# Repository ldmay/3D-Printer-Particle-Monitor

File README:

Overview

This project implements an air quality monitor system to monitor 3D printing emissions using an ESP32, BME680, SGP40, and SPS30 sensors. 

3D printing emissions are typically broken down into volatile organic compounds (VOC) and ultrafine particles. These can be harmful when inhaled and are associated with higher risks for various medical conditions. The sensors used were chosen to detect these matters. 

Hardware

The project uses an ESP32-WROVER-B mounted on the ESP32 DevKit C. This provides a microcontroller a variety of peripherals to connect the sensors, as well as WIFI capabilities to host its own webserver. 

The BME680 is a general atmospheric condition sensor. It can detect a variety of atmospheric conditions, including temperature and humidity, which is required for the operation of the SGP40. It also returns a rough indication of VOC count using its gas resistance measurement, which can be compared to the VOC index calculated by the SGP40. Gas resistance is measured in kOhm. The absolute value is meaningless, but deviation over time represents an increase or decrease in VOCs. A lower resistance denotes an increase in VOC count. 
The BSEC library allows for more precise VOC measurements. I plan to include it in the future. 

The SGP40 is used to detect VOCs. Given temperature and humidity inputs, it returns a VOC index between 1 (ideal air quality) and 500 (very poor air quality). This index has a baseline of 100, and deviations represent changes in VOC over time. 

The SPS30 sensor is used to determine ultrafine particle concentrations. It detects particle numbers concentrations in the range of 0-3000/cm³ and mass concentrations in the range of  1-1000µg/m³. It also returns a measure of typical particle size. 
The number and mass concentration outputs represent distinct bins. There are five particle concentration bins - PM0.5 to PM10 - and four mass concentration bins - PM1 to PM10. The number following "PM" refers to the upper bound of the particle diameter range in micrometres (e.g. PM2.5 covers all particles from 0.3 μm up to 2.5 μm in diameter). 

Circuit Description

Sensors are connected to the ESP32 using a shared I2C bus. 

Software Requirements

Project written using PlatformIO. The Arduino IDE can likely also be used, though I have not tested this. 

The following libraries are required: 
lib_deps = 
	adafruit/Adafruit BME680 Library@^2.0.6
	adafruit/Adafruit Unified Sensor
	adafruit/Adafruit BusIO
	adafruit/Adafruit SGP40 Sensor@^1.1.4
	sensirion/Sensirion Gas Index Algorithm
	sensirion/Sensirion I2C SPS30@^1.0.0
	esp32async/ESPAsyncWebServer@^3.10.3
	esp32async/AsyncTCP@^3.4.10

Ignore the following libraries: 
lib_ignore = 
	RPAsyncTCP
	ESPAsyncTCP

Usage

Prior to uploading the code, replace the WIFI_SSID and WIFI_PASS values with your local network credentials. To access the server, you must be connected to the same network as the ESP32. 

By default, the code will update sensor values every second. This can easily be modified by changing the TIMER_DELAY value. The SPS30 sensor cannot measure at a higher frequency than 1Hz. 

Once the circuit is set up and code is loaded to the ESP32, it will begin printing sensor values to the serial monitor. The ESP32 should also automatically set up a web server. The address should be printed to the serial monitor. Navigating to the address will reveal a simple dashboard displaying atmospheric variables and charts showing VOC and particle concentrations. 

Prior to measuring a print, the sensors should be given 5-10 minutes to set up baseline values. VOC measurements display deviation from previous measurements, rather than absolute values.

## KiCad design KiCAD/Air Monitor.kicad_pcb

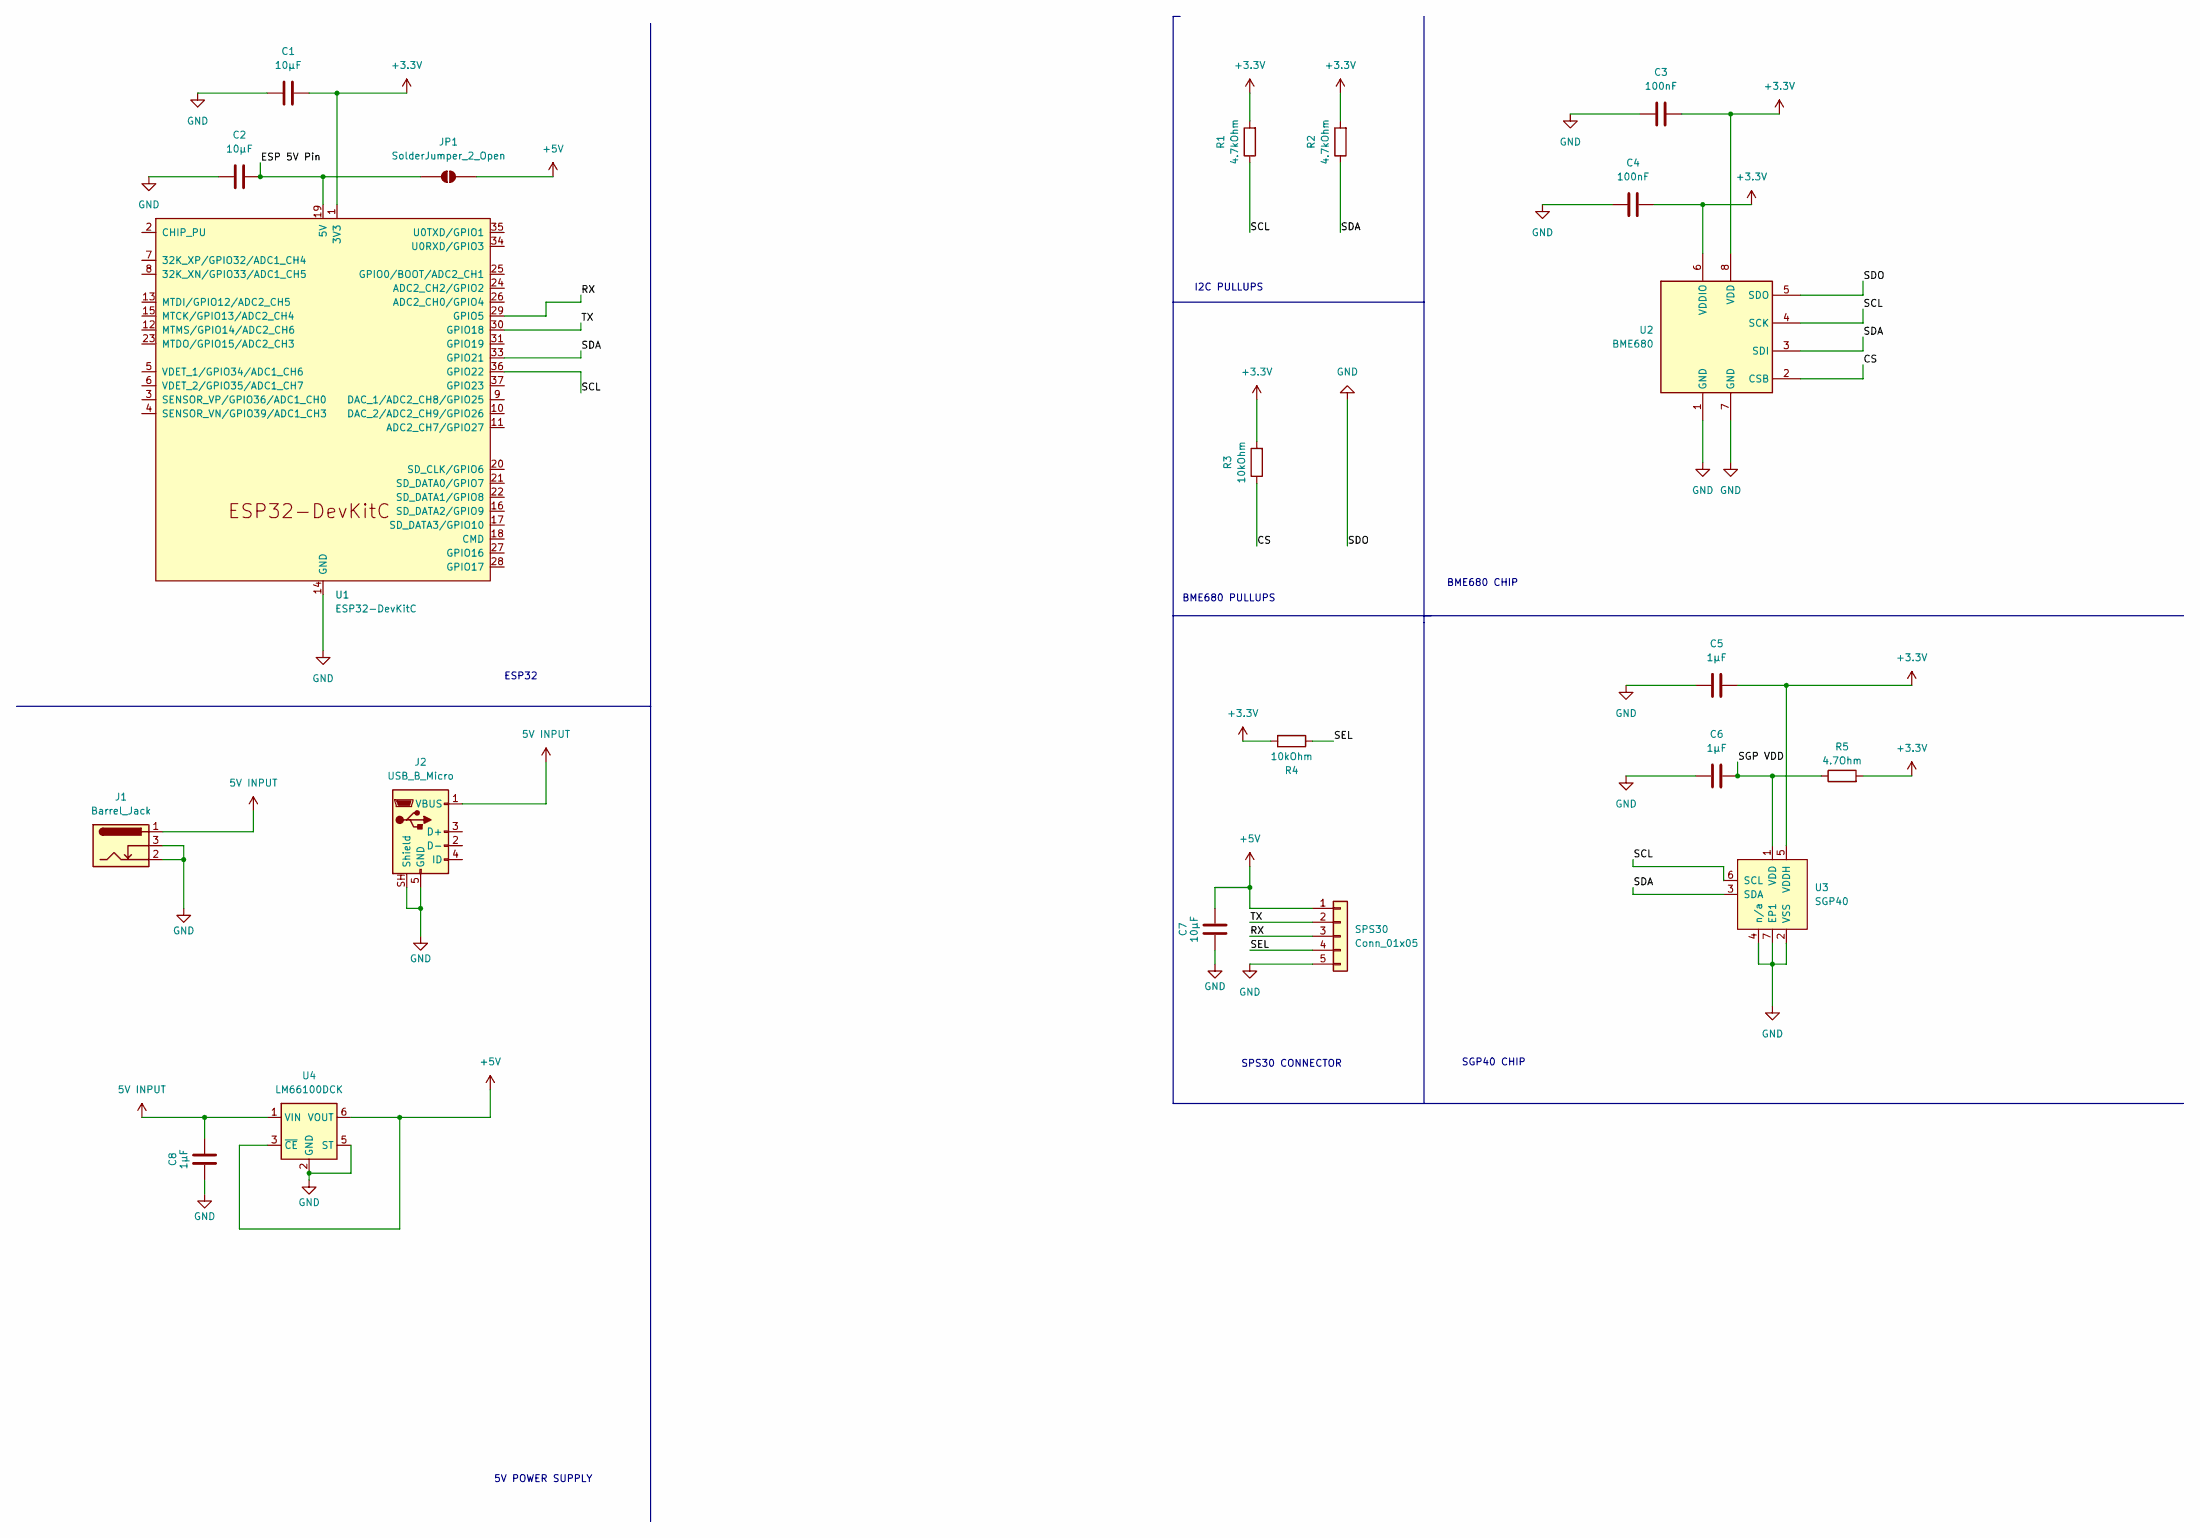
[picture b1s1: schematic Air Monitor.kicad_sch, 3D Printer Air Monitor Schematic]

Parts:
C1, C2, C7: 10μF; C_0402_1005Metric
C3, C4: 100nF; C_0402_1005Metric
C5, C6, C8: 1μF; C_0402_1005Metric
J1: Barrel_Jack; BarrelJack_Wuerth_6941xx301002
J2: USB_B_Micro; USB_Micro-B_Wuerth_629105150521
JP1: SolderJumper_2_Open; SolderJumper-2_P1.3mm_Open_RoundedPad1.0x1.5mm
R1, R2: 4.7kOhm; R_0402_1005Metric
R3, R4: 10kOhm; R_0402_1005Metric
R5: 4.7Ohm; R_0402_1005Metric
SPS30: Conn_01x05; JST_ZH_B5B-ZR_1x05_P1.50mm_Vertical
U1: ESP32-DevKitC; ESP32-DevKitC Shield
U2: BME680; Bosch_LGA-8_3x3mm_P0.8mm_ClockwisePinNumbering
U3: SGP40; Sensirion_DFN-6-1EP_2.44x2.44mm_P0.8mm
U4: LM66100DCK; SOT-363_SC-70-6

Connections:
5V INPUT: C8.2, J1.1, J2.1 (VBUS), U4.1 (VIN)
+3.3V: C1.2, C3.1, C4.1, C5.1, R1.2, R2.2, R3.2, R4.2, R5.2, U1.1 (3V3), U2.6 (VDDIO), U2.8 (VDD), U3.5 (VDDH)
+5V: C7.2, JP1.2 (B), SPS30.1, U4.3 (~CE), U4.6 (VOUT)
/CS: R3.1, U2.2 (CSB)
/ESP 5V Pin: C2.2, JP1.1 (A), U1.19 (5V)
/RX: SPS30.3, U1.29 (GPIO5)
/SCL: R1.1, U1.36 (GPIO22), U2.4 (SCK), U3.6 (SCL)
/SDA: R2.1, U1.33 (GPIO21), U2.3 (SDI), U3.3 (SDA)
/SEL: R4.1, SPS30.4
/SGP VDD: C6.1, R5.1, U3.1 (VDD)
/TX: SPS30.2, U1.30 (GPIO18)
GND: C1.1, C2.1, C3.2, C4.2, C5.2, C6.2, C7.1, C8.1, J1.2, J1.3, J2.5 (GND), J2.SH (Shield), SPS30.5, U1.14 (GND), U1.32 (GND), U1.38 (GND), U2.1 (GND), U2.5 (SDO), U2.7 (GND), U3.2 (VSS), U3.4 (n/a), U3.7 (EP1), U4.2 (GND), U4.5 (ST)

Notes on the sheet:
ESP32
5V POWER SUPPLY
SPS30 CONNECTOR
I2C PULLUPS
BME680 PULLUPS
SGP40 CHIP
BME680 CHIP

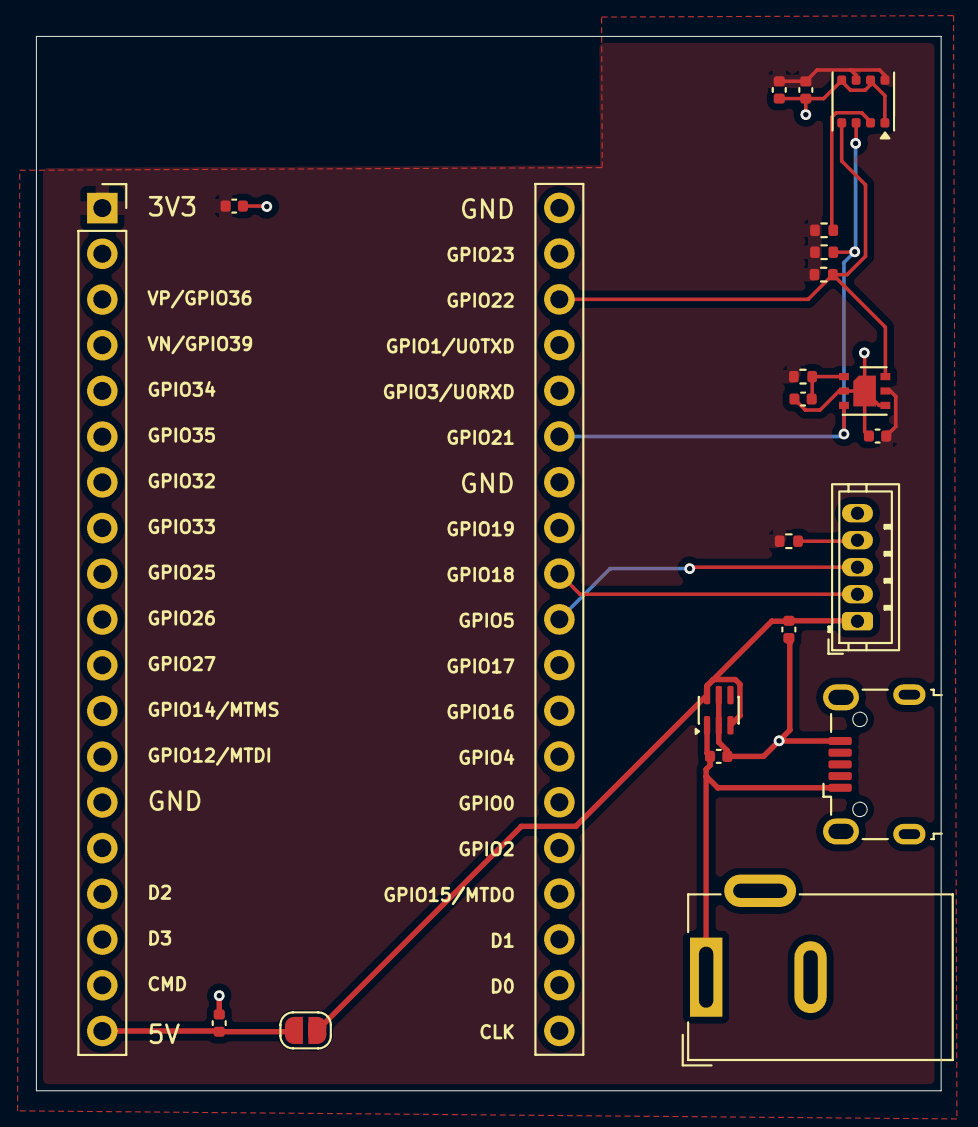
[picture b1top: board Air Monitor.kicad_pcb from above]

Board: 2 copper layers, 50.3 x 58.6 mm, 21 parts (0 on the bottom side), 12 nets.

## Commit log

2026-05-10 Copied repo
2026-05-10 Update with results
2026-05-10 Updated results
2026-06-01 PCB updates
